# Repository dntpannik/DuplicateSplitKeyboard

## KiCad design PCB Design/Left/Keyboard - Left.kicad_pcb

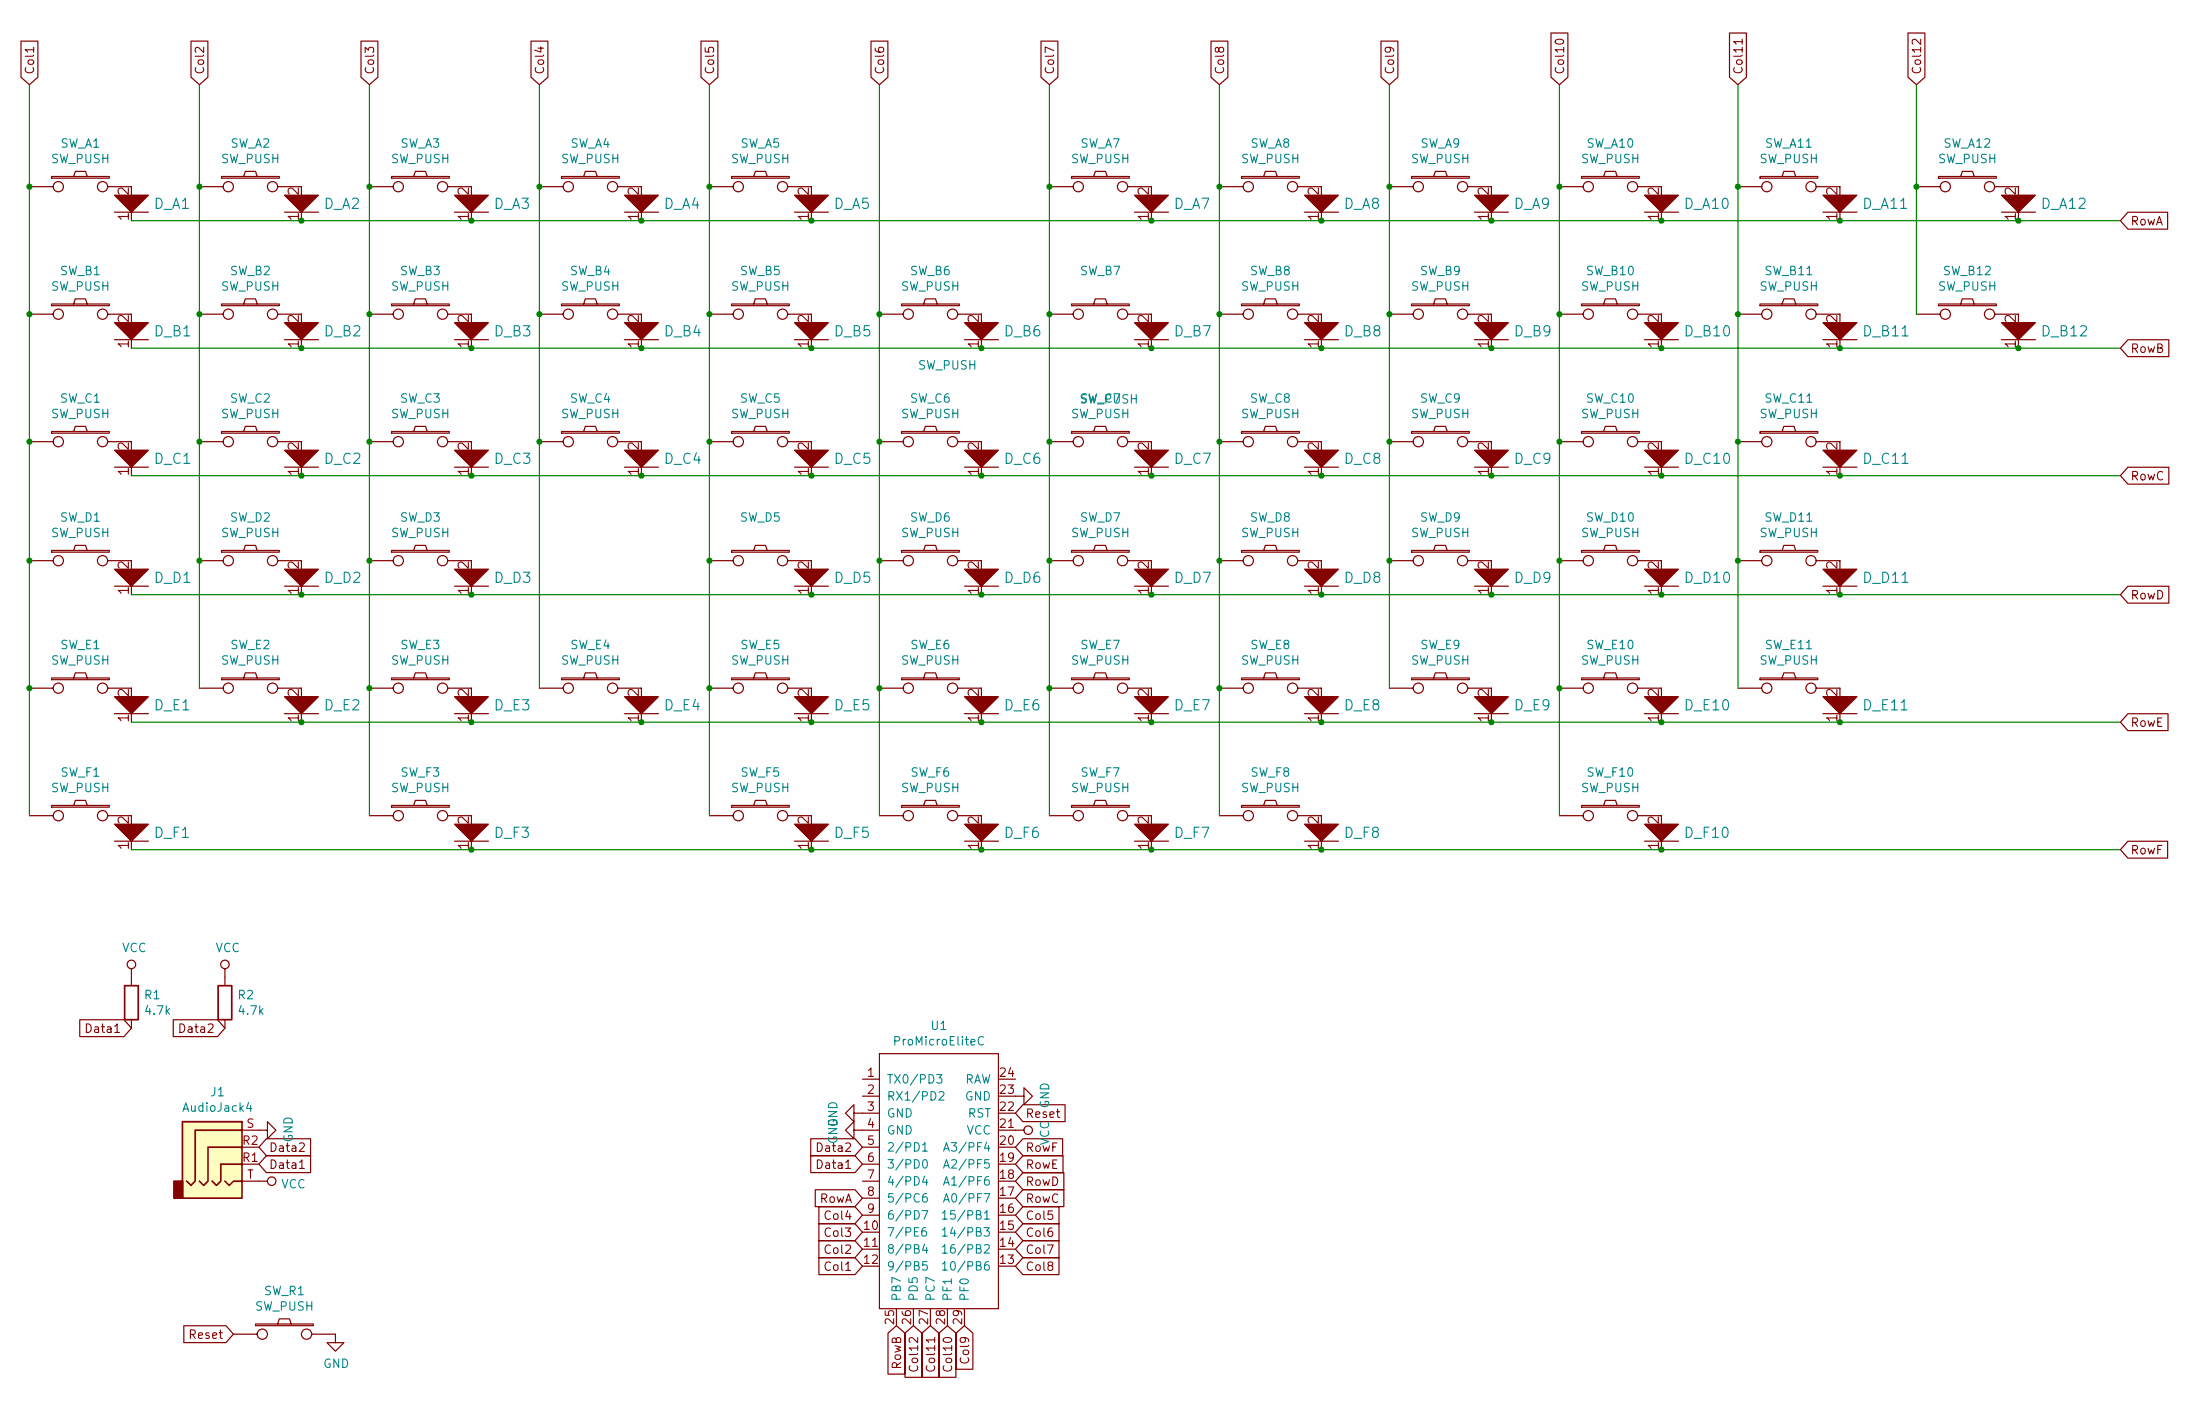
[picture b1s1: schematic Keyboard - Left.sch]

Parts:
D_A1, D_A2, D_A3, D_A4, D_A5, D_A7, D_A8, D_A9, D_A10, D_A11, D_A12: D; ComboDiode
D_B1, D_B2, D_B3, D_B4, D_B5, D_B6, D_B7, D_B8, D_B9, D_B10, D_B11, D_B12: D; ComboDiode
D_C1, D_C2, D_C3, D_C4, D_C5, D_C6, D_C7, D_C8, D_C9, D_C10, D_C11: D; ComboDiode
D_D1, D_D2, D_D3, D_D5, D_D6, D_D7, D_D8, D_D9, D_D10, D_D11: D; ComboDiode
D_E1, D_E2, D_E3, D_E4, D_E5, D_E6, D_E7, D_E8, D_E9, D_E10, D_E11: D; ComboDiode
D_F1, D_F3, D_F5, D_F6, D_F7, D_F8, D_F10: D; ComboDiode
J1: AudioJack4; TRRS-PJ-320A
R1, R2: 4.7k; ComboResistor
SW_A1, SW_A2, SW_A3, SW_A4, SW_A5, SW_A7, SW_A8, SW_A9, SW_A10, SW_A11, SW_A12: SW_PUSH; SW_Cherry_MX_1.00u_PCB
SW_B1, SW_B2, SW_B3, SW_B4, SW_B5, SW_B6, SW_B7, SW_B8, SW_B9, SW_B10, SW_B11, SW_B12: SW_PUSH; SW_Cherry_MX_1.00u_PCB
SW_C1, SW_C2, SW_C3, SW_C6, SW_C7, SW_C8, SW_C9, SW_C10, SW_C11: SW_PUSH; SW_Cherry_MX_1.00u_PCB
SW_C4: SW_PUSH; SW_Cherry_MX_2.00u_Vertical_PCB
SW_C5: SW_PUSH; SW_Cherry_MX_1.50u_PCB
SW_D1, SW_D2, SW_D3, SW_D6, SW_D7, SW_D8, SW_D9, SW_D10, SW_D11: SW_PUSH; SW_Cherry_MX_1.00u_PCB
SW_D5: SW_PUSH; SW_Cherry_MX_1.75u_PCB
SW_E1, SW_E2, SW_E3, SW_E6, SW_E7, SW_E8, SW_E9, SW_E10, SW_E11: SW_PUSH; SW_Cherry_MX_1.00u_PCB
SW_E4: SW_PUSH; SW_Cherry_MX_2.00u_Vertical_PCB
SW_E5: SW_PUSH; SW_Cherry_MX_2.25u_PCB
SW_F1: SW_PUSH; SW_Cherry_MX_2.00u_PCB
SW_F3: SW_PUSH; SW_Cherry_MX_1.00u_PCB
SW_F5, SW_F6, SW_F7, SW_F8: SW_PUSH; SW_Cherry_MX_1.25u_PCB
SW_F10: SW_PUSH; SW_Cherry_MX_2.75u_PCB
SW_R1: SW_PUSH; SW_Tactile_SPST_Angled_PTS645Vx39-2LFS
U1: ProMicroEliteC; Elite-C

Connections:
Col1: SW_A1.1, SW_B1.1, SW_C1.1, SW_D1.1, SW_E1.1, SW_F1.1, U1.12 (9/PB5)
Col2: SW_A2.1, SW_B2.1, SW_C2.1, SW_D2.1, SW_E2.1, U1.11 (8/PB4)
Col3: SW_A3.1, SW_B3.1, SW_C3.1, SW_D3.1, SW_E3.1, SW_F3.1, U1.10 (7/PE6)
Col4: SW_A4.1, SW_B4.1, SW_C4.1, SW_E4.1, U1.9 (6/PD7)
Col5: SW_A5.1, SW_B5.1, SW_C5.1, SW_D5.1, SW_E5.1, SW_F5.1, U1.16 (15/PB1)
Col6: SW_B6.1, SW_C6.1, SW_D6.1, SW_E6.1, SW_F6.1, U1.15 (14/PB3)
Col7: SW_A7.1, SW_B7.1, SW_C7.1, SW_D7.1, SW_E7.1, SW_F7.1, U1.14 (16/PB2)
Col8: SW_A8.1, SW_B8.1, SW_C8.1, SW_D8.1, SW_E8.1, SW_F8.1, U1.13 (10/PB6)
Col9: SW_A9.1, SW_B9.1, SW_C9.1, SW_D9.1, SW_E9.1, U1.29 (PF0)
Col10: SW_A10.1, SW_B10.1, SW_C10.1, SW_D10.1, SW_E10.1, SW_F10.1, U1.28 (PF1)
Col11: SW_A11.1, SW_B11.1, SW_C11.1, SW_D11.1, SW_E11.1, U1.27 (PC7)
Col12: SW_A12.1, SW_B12.1, U1.26 (PD5)
Data1: J1.R1, R1.2, U1.6 (3/PD0)
Data2: J1.R2, R2.2, U1.5 (2/PD1)
GND: J1.S, SW_R1.2, U1.3 (GND), U1.4 (GND), U1.23 (GND)
unnamed: D_A1.2, SW_A1.2
unnamed: D_A2.2, SW_A2.2
unnamed: D_A3.2, SW_A3.2
unnamed: D_A4.2, SW_A4.2
unnamed: D_A5.2, SW_A5.2
unnamed: D_A7.2, SW_A7.2
unnamed: D_A8.2, SW_A8.2
unnamed: D_A9.2, SW_A9.2
unnamed: D_A10.2, SW_A10.2
unnamed: D_A11.2, SW_A11.2
unnamed: D_A12.2, SW_A12.2
unnamed: D_B1.2, SW_B1.2
unnamed: D_B2.2, SW_B2.2
unnamed: D_B3.2, SW_B3.2
unnamed: D_B4.2, SW_B4.2
unnamed: D_B5.2, SW_B5.2
unnamed: D_B6.2, SW_B6.2
unnamed: D_B7.2, SW_B7.2
unnamed: D_B8.2, SW_B8.2
unnamed: D_B9.2, SW_B9.2
unnamed: D_B10.2, SW_B10.2
unnamed: D_B11.2, SW_B11.2
unnamed: D_B12.2, SW_B12.2
unnamed: D_C1.2, SW_C1.2
unnamed: D_C2.2, SW_C2.2
unnamed: D_C3.2, SW_C3.2
unnamed: D_C4.2, SW_C4.2
unnamed: D_C5.2, SW_C5.2
unnamed: D_C6.2, SW_C6.2
unnamed: D_C7.2, SW_C7.2
unnamed: D_C8.2, SW_C8.2
unnamed: D_C9.2, SW_C9.2
unnamed: D_C10.2, SW_C10.2
unnamed: D_C11.2, SW_C11.2
unnamed: D_D1.2, SW_D1.2
unnamed: D_D2.2, SW_D2.2
unnamed: D_D3.2, SW_D3.2
unnamed: D_D5.2, SW_D5.2
unnamed: D_D6.2, SW_D6.2
unnamed: D_D7.2, SW_D7.2
unnamed: D_D8.2, SW_D8.2
unnamed: D_D9.2, SW_D9.2
unnamed: D_D10.2, SW_D10.2
unnamed: D_D11.2, SW_D11.2
unnamed: D_E1.2, SW_E1.2
unnamed: D_E2.2, SW_E2.2
unnamed: D_E3.2, SW_E3.2
unnamed: D_E4.2, SW_E4.2
unnamed: D_E5.2, SW_E5.2
unnamed: D_E6.2, SW_E6.2
unnamed: D_E7.2, SW_E7.2
unnamed: D_E8.2, SW_E8.2
unnamed: D_E9.2, SW_E9.2
unnamed: D_E10.2, SW_E10.2
unnamed: D_E11.2, SW_E11.2
unnamed: D_F1.2, SW_F1.2
unnamed: D_F3.2, SW_F3.2
unnamed: D_F5.2, SW_F5.2
unnamed: D_F6.2, SW_F6.2
unnamed: D_F7.2, SW_F7.2
unnamed: D_F8.2, SW_F8.2
unnamed: D_F10.2, SW_F10.2
Reset: SW_R1.1, U1.22 (RST)
RowA: D_A1.1, D_A2.1, D_A3.1, D_A4.1, D_A5.1, D_A7.1, D_A8.1, D_A9.1, D_A10.1, D_A11.1, D_A12.1, U1.8 (5/PC6)
RowB: D_B1.1, D_B2.1, D_B3.1, D_B4.1, D_B5.1, D_B6.1, D_B7.1, D_B8.1, D_B9.1, D_B10.1, D_B11.1, D_B12.1, U1.25 (PB7)
RowC: D_C1.1, D_C2.1, D_C3.1, D_C4.1, D_C5.1, D_C6.1, D_C7.1, D_C8.1, D_C9.1, D_C10.1, D_C11.1, U1.17 (A0/PF7)
RowD: D_D1.1, D_D2.1, D_D3.1, D_D5.1, D_D6.1, D_D7.1, D_D8.1, D_D9.1, D_D10.1, D_D11.1, U1.18 (A1/PF6)
RowE: D_E1.1, D_E2.1, D_E3.1, D_E4.1, D_E5.1, D_E6.1, D_E7.1, D_E8.1, D_E9.1, D_E10.1, D_E11.1, U1.19 (A2/PF5)
RowF: D_F1.1, D_F3.1, D_F5.1, D_F6.1, D_F7.1, D_F8.1, D_F10.1, U1.20 (A3/PF4)
VCC: J1.T, R1.1, R2.1, U1.21 (VCC)

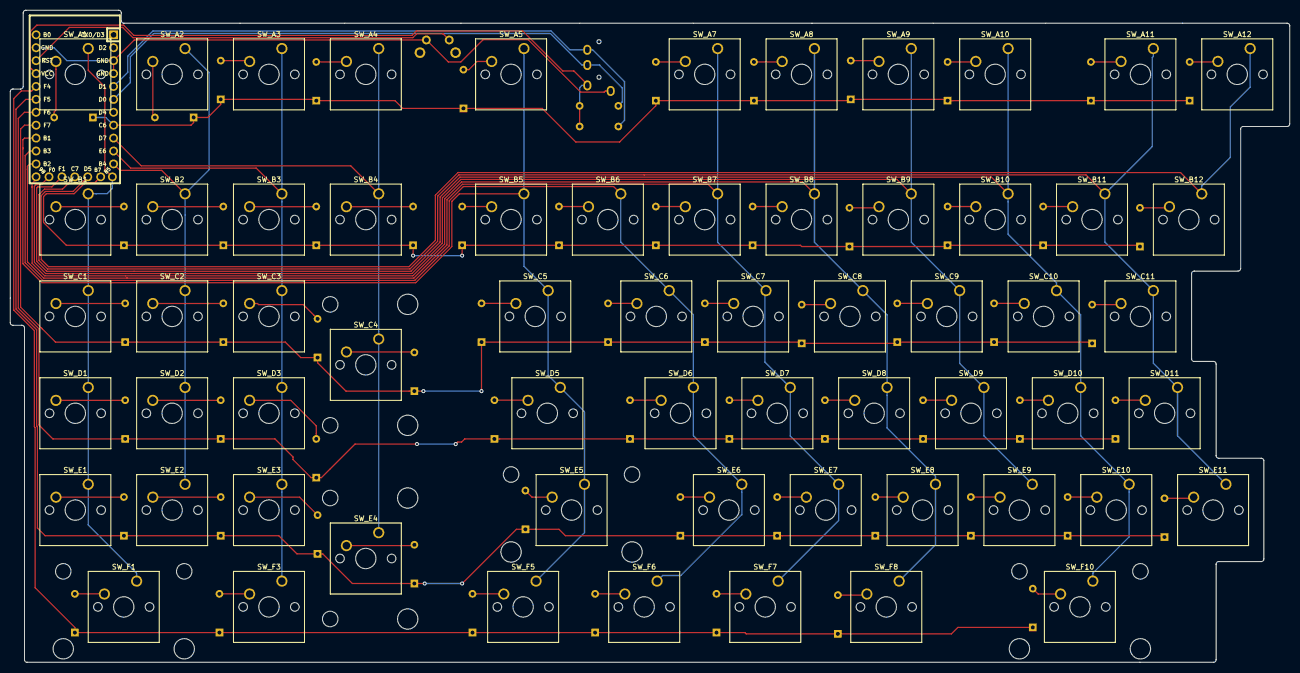
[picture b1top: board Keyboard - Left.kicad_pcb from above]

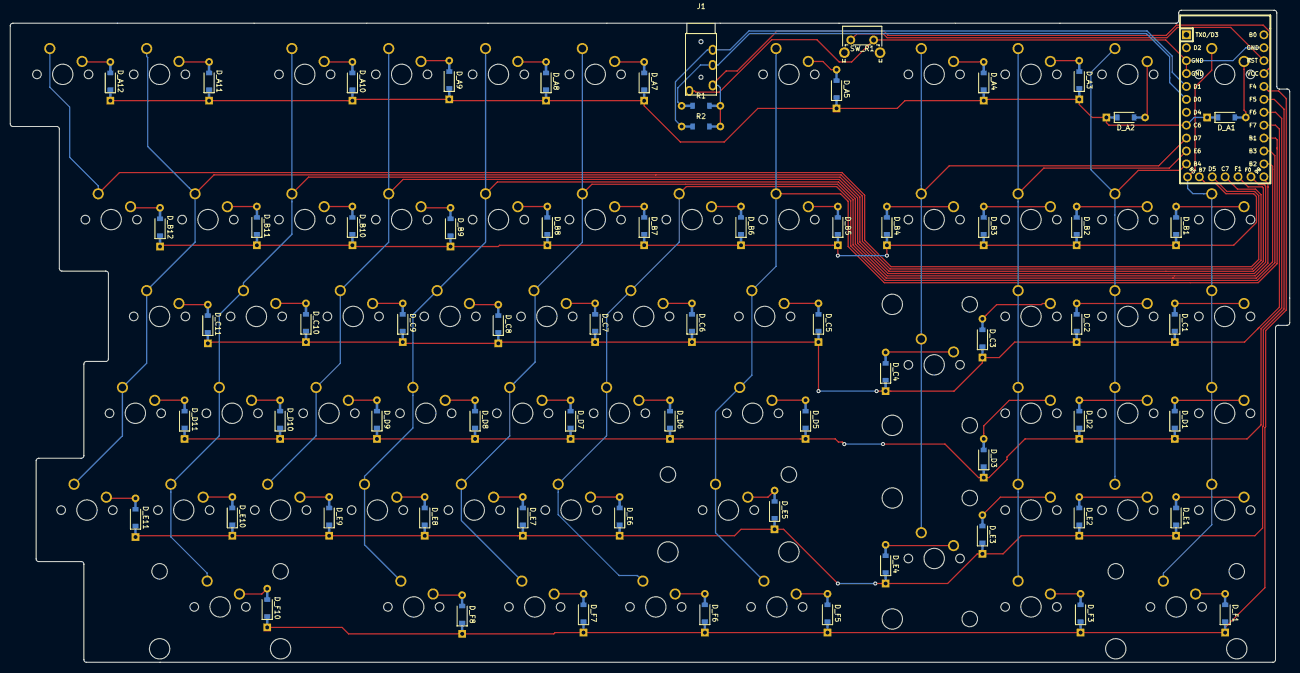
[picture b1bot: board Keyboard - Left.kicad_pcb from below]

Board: 2 copper layers, 251.7 x 128.3 mm, 129 parts (3 on the bottom side), 85 nets.

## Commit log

2019-10-08 Added Readme
2019-10-08 Added PCB Design for Right Half
2019-10-08 Added JSON file of keyboard layout
2019-10-08 Updated keyboard layout and added png file
2019-10-08 Organized pcb design files
2019-10-08 Updated PCB files
2019-10-10 Added Left information. Tweaks to right side
2019-10-23 reworking pcb
2019-10-25 Updated Right PCB
2019-10-26 Finished PCBs, added DXF and Gerber files
2019-11-06 added QMK
